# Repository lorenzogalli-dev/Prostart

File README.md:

# Prostart

**Reaction time and photo finish for every track, for the price of a pair of spikes.**

A start unit that mounts on any starting block, and a phone app that turns a smartphone into a photo finish. The unit sounds the start commands, detects the push-off with an accelerometer and judges the start on its own clock; the phone times the chest crossing the line from the same "go".

Course project, Technology and Health, KTH Royal Institute of Technology, HT26: Arianna Bartocci, Duarte Chambel, Lorenzo Galli, Loke Enlund Östangård, Ninad Purekar. Full write-up: [`Papers/Final Paper/CM2024_Sprint_Start_Final_Paper.pdf`](Papers/Final%20Paper/CM2024_Sprint_Start_Final_Paper.pdf).

## How it works

```
 start unit (on the block)                           phone (at the finish)
 ESP32-C3 + BMI270, 803 Hz  ──── BLE: events, clock sync, run data ────  Flutter app, camera 240 fps
```

- **Start sequence.** Button → 3 s countdown → "on your marks" → "set" 20-25 s later → the unit waits until the athlete is still (< 15 mg for 200 ms) and fires "go" a random 0.7-1.5 s later. Each beep (4 kHz piezo) is started by two register writes and timestamped at that instant.
- **Onset detection.** Every accelerometer sample is timestamped in an interrupt (1 µs clock) and buffered in the sensor's FIFO, so radio traffic can delay a sample but never shift or lose it. Gravity is removed as a vector, so the mounting angle does not matter. An STA/LTA trigger decides *that* the athlete moved; an AIC picker then finds *when*, with no threshold, so the onset does not drift with the trigger level. Under 100 ms after "go" is a false start.
- **App.** *Reaction* mode mirrors the unit and saves every run as CSV. *Photofinish* mode syncs the phone's clock to the unit over BLE, films the line at the highest frame rate with a short exposure, finds the chest front with MediaPipe Pose and the body silhouette, and interpolates the crossing between frames. The time is rounded up to the hundredth, as the rules prescribe.

## Results

| | |
|---|---|
| Sampling | 803.2 Hz, no gaps, 0.9 µs timestamp jitter (2.8 µs with BLE connected) |
| Unit resolution | one sample, 1.2 ms; board and offline detector agree to the sample |
| Reaction time vs 240 fps video (LED at "go") | within ~8 ms, the resolution of the video reference |
| Finish time vs 60 fps reference | 10 ms (hand timing on the same runs: ~0.24 s fast) |
| Onset vs trigger threshold (10-50 mg, 79 starts) | same sample in 70 starts; a threshold-only detector drifts a median 9.3 ms |

**Limits.** Direct BLE reaches ~30 m; a full 100 m needs a finish relay (a second ESP32-C3 on long-range ESP-NOW, field-tested to 100-110 m). One athlete per run. The BMI270 filter delay and the sound's travel time (2.9 ms/m) are not yet measured.

## Hardware and cost

Parts for one start unit, one-off retail prices (estimates):

| Part | SEK |
|---|---:|
| ESP32-C3 SuperMini | 40 |
| BMI270 accelerometer breakout | 100 |
| 1.77" ST7735 TFT | 70 |
| Push button, 12 mm piezo, capacitors | 20 |
| Two-layer PCB (65.5 × 34 mm, batch of 5) | 30 |
| 3D-printed box, lid and button cap (PLA) | 15 |
| Strap to the block | 20 |
| **Total** | **≈ 295** |

For now the unit runs from a USB power bank; the next version will have a built-in LiPo cell and charger (~60 SEK more). The phone is the athlete's own. A single-block commercial reaction timer lists at about US$1,600 (~17,000 SEK); certified competition systems cost far more.

## Business plan

Customers: athletics clubs, school and university teams, coaches and individual sprinters who today time by hand.

| Product | Price | Notes |
|---|---:|---|
| Start unit | 1,290 SEK | ~350 SEK cost at 1,000 units incl. assembly and test: ~70 % gross margin |
| App, Free | 0 | Reaction time, run history, manual photo finish (tap the crossing frame) |
| App, Pro | 49 SEK/month or 399 SEK/year | AI photo finish, analysis of recorded videos, data export |
| Club plan | 1,990 SEK/year | Pro for up to 30 athletes, squad dashboard |

**Rough year-3 projection** (Nordics first, then Europe; assumptions, not market research):

| Line | Volume | Revenue (SEK) |
|---|---:|---:|
| Start units | 3,000 | 3.9 M |
| Pro subscriptions | 1,500 | 0.6 M |
| Club plans | 150 | 0.3 M |
| **Total** | | **≈ 4.8 M** |

Gross profit ≈ 3.7 M SEK after 1.05 M of unit cost, against ~1.5 M SEK/year for a small team (firmware, app, support), after an initial ~1 M SEK to build the finish relay, certify (CE/RED) and tool a moulded enclosure.

## Repository

```
Arduino/AlgorithmRealTimeESP32/  firmware (ESP32-C3 + BMI270, BLE); INFO.md: wiring, build, tests
Arduino/AlgorithmRealTime/       first prototype (XIAO nRF52840 Sense), same detector
Arduino/EspNowLrTest/            long-range ESP-NOW field test (finish relay)
Arduino/WifiFieldTest/           Wi-Fi range field test
prostart/                        Flutter app + native camera plugin (photo finish)
AI_Torso_Detector/               photo-finish reference in Python (MediaPipe)
Hardware/                        KiCad PCB, Gerbers, BOM; enclosure STL files
Data/                            block-start captures
Docs/                            algorithm, build and run notes, figures
Papers/                          final paper (LaTeX, PDF, slides), half-time paper
```

- **Firmware:** `arduino-cli compile --fqbn esp32:esp32:nologo_esp32c3_super_mini Arduino/AlgorithmRealTimeESP32` (ESP32 core 3.3.x), then `arduino-cli upload` with the same FQBN and `-p <port>`.
- **App:** `cd prostart && flutter pub get && flutter run` (iOS tested on an iPhone 13).

## License

All rights reserved: see [LICENSE](LICENSE). The code is visible for academic assessment only; no use, copy, modification or commercial use without the authors' written permission. Third-party code keeps its own license: `Arduino/libraries/Seeed_Arduino_LSM6DS3` (MIT), Bosch's BMI270 configuration in `Bmi270Config.h` (BSD-3-Clause).

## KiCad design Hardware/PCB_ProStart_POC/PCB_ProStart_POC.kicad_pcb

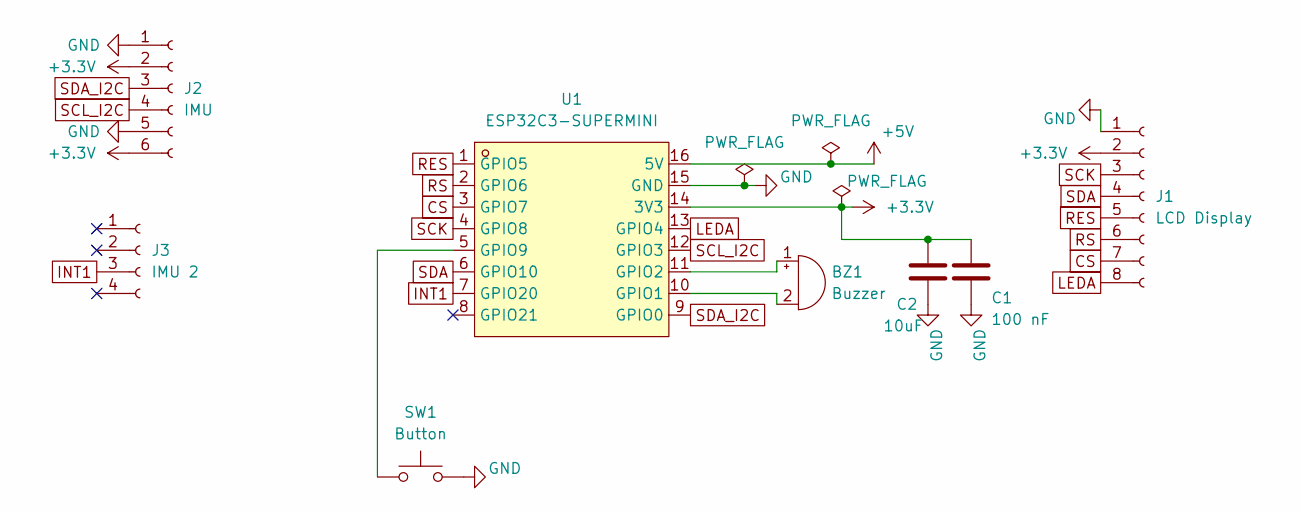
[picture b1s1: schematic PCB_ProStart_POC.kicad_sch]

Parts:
BZ1: Buzzer; Buzzer_12x9.5RM7.6
C1: 100 nF; C_Disc_D3.8mm_W2.6mm_P2.50mm
C2: 10uF; CP_Radial_D5.0mm_P2.00mm
J1: LCD Display; PinSocket_1x08_P2.54mm_Vertical
J2: IMU; PinSocket_1x06_P2.54mm_Vertical
J3: IMU 2; PinSocket_1x04_P2.54mm_Vertical
SW1: Button; SW_PUSH_6mm
U1: ESP32C3-SUPERMINI; DIP-ESP; MPN ESP32C3-SuperMini; LCSC Part C9900147397

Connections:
+3.3V: C1.1, C2.1, J1.2, J2.2, J2.6, U1.14 (3V3)
+5V: U1.16 (5V)
CS: J1.7, U1.3 (GPIO7)
GND: C1.2, C2.2, J1.1, J2.1, J2.5, SW1.2, U1.15 (GND)
INT1: J3.3 (Pin_3_3), U1.7 (GPIO20)
LEDA: J1.8, U1.13 (GPIO4)
unnamed: BZ1.1 (+), U1.11 (GPIO2)
unnamed: BZ1.2 (-), U1.10 (GPIO1)
unnamed: SW1.1, U1.5 (GPIO9)
RES: J1.5, U1.1 (GPIO5)
RS: J1.6, U1.2 (GPIO6)
SCK: J1.3, U1.4 (GPIO8)
SCL_I2C: J2.4, U1.12 (GPIO3)
SDA: J1.4, U1.6 (GPIO10)
SDA_I2C: J2.3, U1.9 (GPIO0)

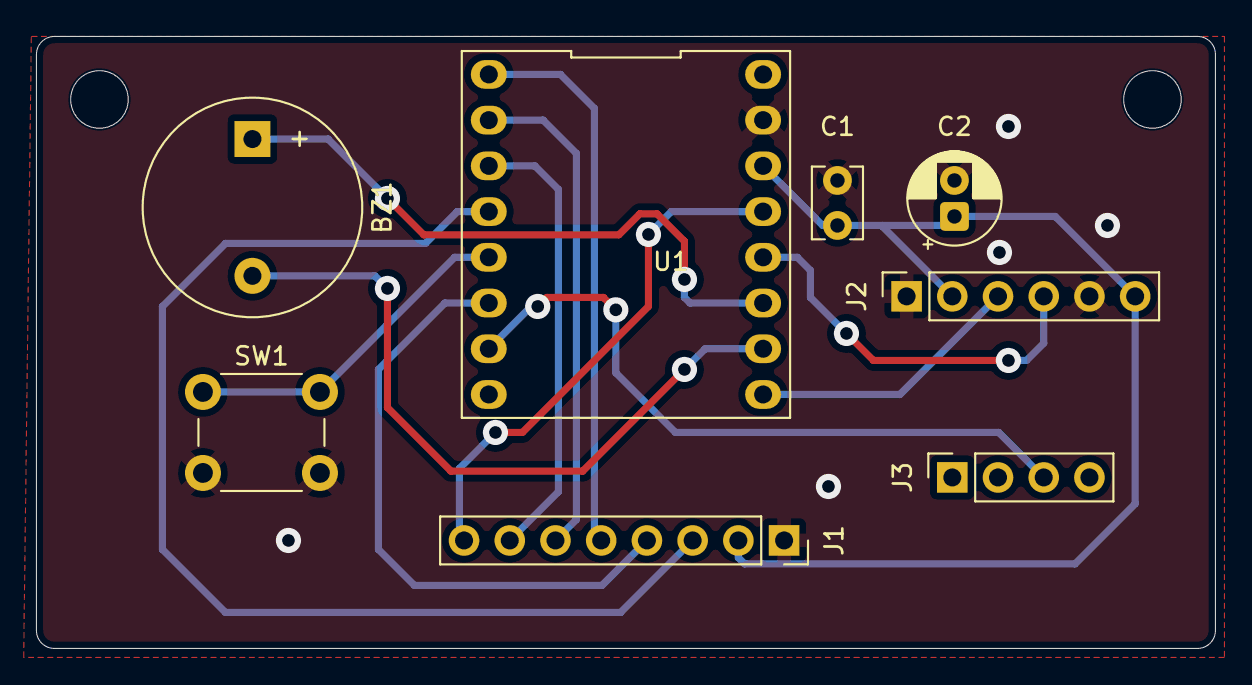
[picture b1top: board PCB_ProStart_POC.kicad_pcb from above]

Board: 2 copper layers, 65.5 x 34.0 mm, 8 parts (0 on the bottom side), 14 nets.

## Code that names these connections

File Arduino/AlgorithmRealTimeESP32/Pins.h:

#pragma once
// ---------------------------------------------------------------------------
// Pins.h - every GPIO this sketch uses on the ESP32-C3 SuperMini, in one place.
// Wiring table and the reasons behind it: INFO.md.
//
// The C3 routes I2C, SPI and LEDC to any pin through its GPIO matrix, so what
// decides this map is the board layout plus four hardware facts:
//   - GPIO2, 8, 9 are boot strapping pins. GPIO9 must read HIGH at reset (it is
//     also the BOOT button) and GPIO8 carries the onboard blue LED to 3V3.
//     Nothing here may pull them at reset.
//   - Only GPIO0-5 can wake the chip from deep sleep. The button is on 9, so
//     "off" is light sleep instead, which any GPIO can wake (enterSystemOff).
//   - GPIO20/21 are UART0, and the ROM prints its boot log on 21: an input
//     driven from outside (INT1) goes on 20, never on 21.
//   - The IMU's SDA/SCL are fixed by the hardware already built: GPIO0/GPIO3.
// ---------------------------------------------------------------------------
#include <stdint.h>

// BMI270 breakout (I2C, address 0x68: SDO to GND)
static const int IMU_SDA_PIN  = 0;
static const int IMU_SCL_PIN  = 3;
static const int IMU_INT1_PIN = 20;  // data-ready. UART0 RX, an input at boot,
                                     // so no clash with a BMI270 still driving
                                     // it across a reset

// Button to GND, INPUT_PULLUP (the board's BOOT button is on the same pin).
// Held at reset or power-up it enters download mode: that is the C3's
// strapping, not the firmware. Release and reset to get out.
static const int BUTTON_PIN = 9;

// Passive piezo, antiphase, no GND. GPIO2 is a strapping pin, safe here:
// a piezo is a capacitor and does not pull it at reset.
static const int BUZZER_PIN   = 1;   // (+)
static const int BUZZER_PIN_B = 2;   // (-)

// 1.77" ST7735S, SPI through the GPIO matrix.
static const int TFT_SCK_PIN  = 8;   // also the blue LED (to 3V3): SPI mode 3
                                     // keeps the clock idle HIGH, LED off
static const int TFT_MOSI_PIN = 10;  // display pin "SDA"
static const int TFT_CS_PIN   = 7;
static const int TFT_DC_PIN   = 6;   // display pin "RS"
static const int TFT_RST_PIN  = 5;
static const int TFT_BL_PIN   = 4;   // display pin "LEDA", through its Q1

// Sync-test LED (green, anode via 100-220 Ohm, cathode to GND): lit with the
// "go" beep, so a camera can see the go instant. GPIO21 is UART0 TX: it
// flickers with the ROM boot log at every reset, then the sketch drives it LOW.
static const int SYNC_LED_PIN = 21;

// Free: none.

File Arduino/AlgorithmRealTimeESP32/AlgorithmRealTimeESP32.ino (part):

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//     writes at the instant of the beep). Pins rest HIGH, not LOW.
//   - Display: mbed::SPI -> SPIClass. Storage: QSPI -> internal flash (v6: none).
//   - Off: nRF System OFF -> ESP32 light sleep, woken by the button (on
//     GPIO9, which cannot wake deep sleep), then a restart.
//   - Dump header gains SENSOR,bmi270 and ODR,800 so a capture says where it
//     came from.
//   - Samples come out of the BMI270's FIFO, not its data registers, and
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              "Bmi270.h configures 800 Hz; change both together");
static const uint32_t SAMPLE_PERIOD_US = 1000000UL / ACCEL_ODR_HZ;

// The IMU's data-ready line: BMI270 INT1 -> IMU_INT1_PIN (Pins.h).

// XIAO: DRDY was level-latched and a missed edge stopped sampling until a
// watchdog read. ESP32: the BMI270's non-latched data-ready keeps pulsing
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//              already cannot supply.
//   PWM      - not tone(). See beep() for why that matters to the measurement.
//
// WIRING: buzzer (+) -> GPIO1, buzzer (-) -> GPIO2. No connection to GND.
// 4000 Hz is this buzzer's measured resonance, not a round number. A frequency
// sweep on 2026-09-11 (Arduino/BuzzerSweep) found a clear peak at 4000 Hz with
// weaker secondary modes at 1600 and 4700; the previous 3000 Hz sat off the
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
    Serial.print("IMU OK - BMI270 accel ");
    Serial.print(ACCEL_ODR_HZ);
    Serial.print(" Hz (data-ready on INT1, GPIO");
    Serial.print(IMU_INT1_PIN);
    Serial.print("), +/-");
    Serial.print(ACCEL_RANGE_G);
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// phase of the 4 kHz wave relative to that instant is random (0-125 us);
// on the XIAO the sequence restarted from a fixed phase.
//
// Rest HIGH, not LOW as on the XIAO: chosen when the buzzer was on GPIO8, which
// also drives the SuperMini's blue LED to 3V3. On GPIO1/2 either level would
// do; both pins at the same level is what keeps the piezo free of DC bias.
static const ledc_timer_t   BUZZER_TIMER = LEDC_TIMER_3;     // far end, as PWM2 was
static const ledc_channel_t BUZZER_CH    = LEDC_CHANNEL_5;
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
// ===========================================================================
// Power: "off" is the ESP32-C3's light sleep - CPU paused, RAM kept, woken by
// the button. Not deep sleep: only GPIO0-5 can wake that, and the button is on
// GPIO9. A press must then be held 1.5 s (dark until then, beep when accepted)
// or the chip goes straight back to sleep. Accepted -> wait for the release
// and restart, so "on" always runs the same setup() as a power-up. The release
// comes first because GPIO9 is the BOOT strap: held across the reset it would
// enter download mode. Light sleep costs more than deep sleep (~0.1-0.2 mA),
// but the SuperMini's red power LED, always on, costs more than either.
// ===========================================================================
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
